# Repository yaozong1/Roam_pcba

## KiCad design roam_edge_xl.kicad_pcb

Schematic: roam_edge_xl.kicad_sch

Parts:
C1, C5, C48: 100nF; C_0402_1005Metric; MPN CL05B104KO5NNNC; LCSC Part C1525; not fitted
C2, C116: 100pf; C_0402_1005Metric; MPN 0402CG101J500NT; LCSC Part C1546
C3: 4.7uF; C_0603_1608Metric; MPN CL10A475MA8NQNC; Digi-key PN 445-6853-1-ND
C4, C8, C14, C15, C44, C56, C60, C72, C73, C100, C101, C110, C111, C112, C113, C115: 100nF; C_0402_1005Metric; MPN CL05B104KO5NNNC; LCSC Part C1525
C6: 47uF; L_1206_3216Metric; MPN CL31A476MPHNNNE; LCSC Part C96123
C7, C33, C34, C37: 100nF; C_0402_1005Metric; MPN CL05B104KP5NNNC; LCSC Part C133086
C9: DNP; C_0402_1005Metric; MPN #N/A; LCSC Part #N/A; not fitted
C10, C12, C18, C19, C35, C38, C62, C63: 33pF; L_0402_1005Metric; MPN GRM1555C1E330JA01D; LCSC Part C441758
C13, C24: 100nF; C_0603_1608Metric; Rating 100V, X7R; MPN GRM188R71H104KA93D; LCSC Part C77055
C17, C79: 1nF; C_0603_1608Metric; MPN CC0603KRX7R0BB102; LCSC Part C106247
C20, C25, C26, C27, C103, C104: 22uF; C_0805_2012Metric; MPN CL21A226MOQNNNE; LCSC Part C98190
C21, C81: 10nF; C_0603_1608Metric; MPN CC0603KRX7R0BB103; LCSC Part C107059
C23, C28, C83: 100nF; C_0603_1608Metric; Rating 100V, X7R; MPN CC0603KRX7R0BB104; LCSC Part C113803
C30: 470uF; C_Elec_6.3x7.7; MPN JVJ16V470M6x8; LCSC Part C46550400
C31, C32: 22uF; C_Elec_6.3x7.7; MPN JVJ100V22M6x8; LCSC Part C46550391
C36, C39: 10pF; C_0402_1005Metric; Rating C0G, NP0; MPN GJM1555C1H100FB01D; LCSC Part C782046
C40, C41: 10nF; C_0402_1005Metric; MPN CL05B103KB5NNNC; LCSC Part C15195
C42, C64, C65, C95, C96, C119, C120: 1uF; C_0402_1005Metric; MPN CL05A105KA5NQNC; LCSC Part C52923
C43, C82: 100nF; C_0402_1005Metric; MPN CL05B104KP5NNNC
C45: 10uF; C_0603_1608Metric; Rating X5R; MPN CL10A106MA8NRNC; Digi-key PN 445-6853-1-ND
C49, C67: 1uF; C_0402_1005Metric; MPN CL05A105KA5NQNC; LCSC Part C52923; not fitted
C55: 2.2uF; C_0402_1005Metric; MPN CL05A225MQ5NSNC; LCSC Part C12530
C59, C117: 10uF; C_0603_1608Metric; MPN CL10A106MA8NRNC; Digi-key PN 445-6853-1-ND
C66: 100nF; C_0402_1005Metric; MPN CL05B104KP5NNNC; not fitted
C77, C78: 100pF; C_0603_1608Metric; MPN CC0603JRNPO0BN101; LCSC Part C107033
C102, C108, C109: 10uF; C_0603_1608Metric; MPN CL10A106MO8NQNC; LCSC Part C92487
CP1, CP3: 100u; CP_EIA-6032-28_Kemet-C; MPN 593D107X9010C2TE3; LCSC Part C167094
CR1: SMCJ100A; SMCJSeries_LTF; MPN SMCJ100A
CR2: PLZ15C-G3/H; ZDO_15C-G3&slash_H_VIS; MPN PLZ15C-G3/H
D1: AXGD10402; D_0402_1005Metric; MPN AXGD10402KR; LCSC Part C434715; not fitted
D3, D4: LED; LED_0603_1608Metric; mpn QBLP601D-IB; LCSC Part C2286
D6, D8, D20: D4V5H1BS2LP-7B; D_0402_1005Metric; MPN D4V5H1BS2LP-7B; LCSC Part C5244624
D9: B230; D_SMB; MPN B230
D10: D_Schottky; D_SMA; MPN RB058L150TE25; LCSC Part C3020232
D11: SS10100; D_SMC; MPN SS10100-SMC; LCSC Part C908692
D12: SM712_SOT23; SOT-323_SC-70; MPN ESDCAN03-2BWY; LCSC Part C1973833
D13: AXGD10402; D_0402_1005Metric; MPN AXGD10402KR; LCSC Part C434715
D16: PESD8V0L2BT-N; SOT-23; MPN PESD8V0L2BT-N; LCSC Part C316022; not fitted
D17: BAT54AW; SOT-323_SC-70; MPN BAT54AW; LCSC Part C5186015
D21, D22: ESD56151W04; D_SOD-323; MPN TPESD56151W04; LCSC Part C2841421
D24: PESD3V3L1BA-N; D_SOD-323; MPN PESD3V3L1BA-N; LCSC Part C41409249
F1: Polyfuse; Fuse_1206_3216Metric; MPN SMD1206-300-6; LCSC part number C46641035
FID1, FID2: Fiducial; Fiducial_1mm_Mask2mm; MPN #N/A; LCSC Part #N/A; not fitted
IC4: MAX13487EESA+T; SOIC127P600X175-8N; MPN MAX13487EESA+T; Mouser Part Number 700-MAX13487EESAT; not fitted
J1: Battery; Molex_PicoBlade_53048-0310_1x03_P1.25mm_Horizontal; MPN 1.25T-3P-WP; LCSC Part C2689907
J2, J4: USB_B_Micro; USB_Micro-B_Molex_47346-0001; MPN 47346-0001; LCSC Part C132560; not fitted
J3: IPEX; IPEX-SMD_HC-RF-IPEX0303-01; MPN HC-RF-IPEX0303-01; LCSC Part C2894919
J5: DNP; Solder_conn_10p; not fitted
J6: CA-L01; MPN CA-L01; LCSC Part C2838841
J7: SIM8060-6-0-14-00-A; GCT_SIM8060-6-0-14-00-A; MPN SIM8060-6-0-14-00-A; Mouser Part Number 640-SIM8060601400A
J8: MX23A18NF1; CONN-TH_18P-P2.50_MX23A18NF1; MPN MX23A18NF1
J9: Conn_01x11_Pin; JST_XH_B11B-XH-A_1x11_P2.50mm_Vertical; MPN 2.54mm-11P ZZ; LCSC Part C18185680; not fitted
J11: Conn_01x06_Pin; PinHeader_1x06_P2.54mm_Vertical
JP2: 0; R_0805_2012Metric; MPN RC0805JR-070RL; LCSC Part C96345; not fitted
JP4: SolderJumper_2_Open; SolderJumper-2_P1.3mm_Open_RoundedPad1.0x1.5mm; LCSC Part #N/A; not fitted
JP5: SolderJumper_2_Open; SolderJumper-2_P1.3mm_Open_RoundedPad1.0x1.5mm; not fitted
L1: 2.2uH; L_Bourns-SRN4018; MPN WPN4020H2R2MT; LCSC Part C98361
L2: 18nH; L_0402_1005Metric; MPN LQW15AN18NG80D; LCSC Part C908004
L3: 2.2nH; L_0402_1005Metric; MPN LQW15AN2N2B80D; LCSC Part C2041833
L4: 4.3nH; L_0402_1005Metric; MPN LQG15HS4N3S02D; LCSC Part C97999
L5: 22nH; L_0402_1005Metric; MPN LQW15AN22NG00D; LCSC Part C86129
L6: 68nH; L_0402_1005Metric; MPN SDCL1005C68NJTDF; LCSC Part C32836
L8: 33UH; L_Changjiang_FNR5040S; MPN FNR5040S330MT; LCSC Part C167973
L10, L13: DNP; L_0402_1005Metric; MPN #N/A; LCSC Part #N/A; not fitted
L11: 1uH; IND-SMD_L5.0-W5.0_SPM5030T; MPN SPM5030T-1R0M; LCSC Part C138582
L12: 56UH; L_Changjiang_FXL1040; MPN FXL1040-330-M; LCSC Part C475918
L15: 2.2uH; L_0603_1608Metric; MPN CMH160808B2R2MT; LCSC Part C394950
Q1: SQS201CENW-T1_GE3; PDFN3333-8_L3.1-W3.2-P0.65-LS3.4-BL; MPN SQS201CENW-T1_GE3
Q4, Q5, Q6: Q_NPN_BEC_BRT; SOT-23; MPN KRC106S; LCSC Part C5439972
Q7: 2N7002E; SOT-23; MPN 2N7002E
Q9: AO4407A; AO4407A_SOIC-8_150MIL; Manufacturer_Part_Number AO4407A
R1: 15k; R_0402_1005Metric; MPN 0402WGF1502TCE; LCSC Part C25756
R2, R6, R30, R60: 1K; R_0402_1005Metric; MPN 0402WGF1001TCE; LCSC Part C11702
R3: 1K; R_0402_1005Metric; MPN 0402WGF1001TCE; LCSC Part C11702; not fitted
R4: 0; R_0402_1005Metric; MPN 0402WGF0000TCE; LCSC Part C17168
R5: 100k; R_0402_1005Metric
R7: 200K; R_0402_1005Metric; MPN HPCR0402F200KK9; LCSC Part C364966
R8: 24k; R_0402_1005Metric
R9, R10: 750; R_0603_1608Metric; MPN 0603WAF7500T5E; LCSC Part C23241
R11, R55, R56: 10K; R_0402_1005Metric; MPN 0402WGF1002TCE; LCSC Part C25744
R12, R34, R36, R100: 0; R_0402_1005Metric; MPN RC0402FR-070RL; LCSC Part C106231
R13, R80, R93: 100K; R_0402_1005Metric; MPN 0402WGF1003TCE; LCSC Part C25741
R14: 0.05; R_0805_2012Metric; MPN ERJL06KF50MV; LCSC Part C713441
R15: 12k; R_0402_1005Metric
R17: 169k; R_0402_1005Metric; MPN FRC0402F1693TS; LCSC Part C2974012
R18: 30K; R_0402_1005Metric; MPN RC0402FR-0730KL; LCSC Part C138008
R19, R29, R37, R38: 4K7; R_0402_1005Metric; MPN 0402WGF4701TCE; LCSC Part C25900
R20: 3.6K; R_0402_1005Metric; MPN ERJ2RKF3601X; LCSC Part C413090
R24: 1K; R_0603_1608Metric
R26: 1.2K; R_0402_1005Metric; MPN FRC0402F1201TS; LCSC Part C2909307
R27, R41: 10K; R_0603_1608Metric
R33, R35: 10K; R_0402_1005Metric; MPN 0402WGF1002TCE; LCSC Part C25744; not fitted
R39, R40: 20; R_0402_1005Metric; Tolerance 1%; MPN 0402WGF200JTCE; LCSC Part C25089; not fitted
R43, R45: 4K7; R_0402_1005Metric; MPN 0402WGF4701TCE; LCSC Part C25900; not fitted
R44: DNP; R_0402_1005Metric; MPN #N/A; LCSC Part #N/A; not fitted
R47, R48: 10; R_0402_1005Metric; MPN CRCW040210R0FKED; LCSC Part C481926; not fitted
R57: 680; R_0805_2012Metric; MPN ERJP06J681V; LCSC Part C441734
R58: 100k; R_0402_1005Metric; MPN 667-ERJ-2RKF1003X
R59: 1k; R_0402_1005Metric; MPN PFR05S-102-FNH
R61: 130; R_0603_1608Metric; MPN 0603WAF1300T5E; LCSC Part C22796
R62: 4K7; R_0402_1005Metric; LCSC Part C25900
R79: 649K; R_0402_1005Metric; MPN 0402WGF6493TCE; LCSC Part C423143
R84: 3.9K; R_0402_1005Metric; MPN 0402WGF3901TCE; LCSC Part C51721
R85: 51K; R_0402_1005Metric; MPN 0402WGF5102TCE; LCSC Part C25794
R86: 1.6K; R_0402_1005Metric; MPN 0402WGF1601TCE; LCSC Part C4908
R87: 0.2; R_0805_2012Metric; MPN 0805W8F200LT5E; LCSC Part C44051
R94: 330k; R_0402_1005Metric; MPN RC0402FR-07330KL; LCSC Part C138006
S1: ESE-11MV9; ESE11MV9; MPN ESE-11MV9; Mouser Part Number 667-ESE-11MV9
SW1: SW_Push; SW_Push_SPST_NO_Alps_SKRK; MPN TS-1088-AR02016; LCSC Part C720477
SW2: SW_Push; SW_Push_SPST_NO_Alps_SKRK; MPN TS-1088-AR02016; LCSC Part C720477; not fitted
TP1: TXD; TestPoint_Pad_D1.0mm; MPN #N/A; LCSC Part #N/A; not fitted
TP2, TP4, TP5, TP8, TP16, TP17, TP18, TP23, TP27, TP28: TestPoint; TestPoint_Pad_D1.0mm; MPN #N/A; LCSC Part #N/A; not fitted
TP3: T_BAT; TestPoint_Pad_D1.0mm; MPN #N/A; LCSC Part #N/A
TP6: TestPoint; TestPoint_Pad_D1.0mm; MPN #N/A; LCSC Part #N/A
TP9, TP12: TestPoint; TestPoint_Pad_D1.0mm; not fitted
TP10: RXD; TestPoint_Pad_D1.0mm; MPN #N/A; LCSC Part #N/A; not fitted
TP25, TP26: rs485_tx; TestPoint_Pad_D1.0mm; MPN #N/A; LCSC Part #N/A; not fitted
U1: NUP4202; SOT-363_SC-70-6; MPN NUP4202W1T2G; LCSC Part C22390024
U2: TXB0102DCU; VSSOP-8_2.3x2mm_P0.5mm; MPN TXB0102DCUR; LCSC Part C60709; not fitted
U3: TPS566242DRLR; MPN TPS566242DRLR; LCSC Part C5219277
U4: EG1192L; HTSOP-8-1EP_3.9x4.9mm_P1.27mm_EP2.4x3.2mm; MPN EG1192L; LCSC Part C2987436
U5, U19: LTV-217; SOIC-4_4.55x2.6mm_P1.27mm; MPN LTV-217-TP1-B-G; LCSC Part C481866
U6: W25Q128JVP; WSON-8-1EP_6x5mm_P1.27mm_EP3.4x4.3mm
U7: EG915UEUAC-N05-SNNSA; XCVR_EG915UEUAC-N05-SNNSA; MPN EG915UEUAC-N05-SNNSA; LCSC Part C7471302
U8: USBLC6-2SC6; SOT-23-6; MPN USBLC6-2SC6; LCSC Part C2827654
U10, U21, U27: LP5907MFX-3.3; SOT-23-5; MPN LP5907MFX-3.3/NOPB; LCSC Part C80670
U11: TXB0108RGY; Texas_RGY_R-PVQFN-N20_EP2.05x3.05mm; MPN TXB0108RGYR; LCSC Part C194701
U13: LIS2DH12TR; LIS12DH; MPN LIS2DH12TR; Digi-key PN DNP
U14: CN809L; SOT-23-3; MPN CN809L; LCSC Part C840517
U15, U16: LM66100DCKR; SOT-363_SC-70-6; MPN LM66100DCKR; LCSC Part C2869734
U18: TPS61022; Texas_RWU0007A_VQFN-7_2x2mm_P0.5mm; MPN TPS61022RWUR; LCSC Part C915088
U20: LC760Z; XCVR_LC79H; MPN #N/A; LCSC Part C9900159239
U22: TP4056; TP4056_SOP-8-PP; MPN TP4056; LCSC Part C382139
U25: ESP32-S3-MINI-1; ESP32-S2-MINI-1; MPN ESP32-S3-MINI-1-N8; LCSC Part C2913206
U26: TJA1051T/3; SOIC-8_3.9x4.9mm_P1.27mm; MPN TJA1051T/3; LCSC Part C38695
U28: USBLC6-2SC6; SOT-23-6; MPN USBLC6-2SC6; LCSC Part C2827654; not fitted

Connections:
3V3_ALWAYS_ON: C1.1, C14.1, C24.1, C44.1, C45.1, C96.1, C112.2, C117.1, R11.1, R37.1, R38.1, R55.2, R58.2, TP5.1 (1_1), U2.3 (VCCA), U2.6 (OE), U6.8 (VCC), U10.5 (OUT), U11.19 (V_{CCB}), U13.2 (CS), U13.9 (VDD), U13.10 (VDD_IO), U25.3 (3V3), U26.5 (VIO)
3V3_ANT: R4.2, TP23.1 (1_1), U20.14 (ANT_BIAS)
3V3_LDO: C72.1, C73.1, C120.1, R60.1, TP18.1 (1_1), U19.1, U27.5 (OUT)
4V0: C19.1, C20.1, C25.1, C26.1, C27.1, C33.1, C34.1, C35.1, C36.2, C37.1, C38.1, C39.2, CP1.1, CP3.1, D6.1 (K), L1.2, R17.1, TP8.1 (1_1), U7.32 (VBAT_BB), U7.33 (VBAT_BB), U7.52 (VBAT_RF), U7.53 (VBAT_RF)
4V7_BOOST: C100.1, C103.1, C104.1, R79.1, TP16.1 (1_1), U15.3 (~CE), U16.1 (VIN), U18.3 (VOUT)
5V0: C6.1, C7.1, C64.1, C95.1, C113.2, C119.1, J11.4, JP2.2, R8.1, TP2.1 (1_1), U3.1 (VIN), U10.1 (IN), U14.3 (VCC), U15.6 (VOUT), U16.6 (VOUT), U21.1 (IN), U26.3 (VCC), U27.1 (IN)
5V0_BUCK: C5.1, C30.1, C42.1, C48.1, C49.1, IC4.8 (VCC), JP2.1, L12.2, R3.1, R20.1, R30.2, R33.2, R35.2, R43.2, R87.1, TP27.1 (1_1), U2.7 (VCCB), U15.1 (VIN), U16.3 (~CE)
12V_MCU_OUT: J8.12, J11.5
/3V3_LDO_EN: U25.14 (IO10), U27.3 (EN)
/ACC_INT: U13.12 (INT_1), U25.34 (IO38)
/CAN_500_H: D12.1 (A1), J5.6, J8.2, J9.6, U26.7 (CANH)
/CAN_500_L: D12.2 (A2), J5.5, J8.3, J9.5, U26.6 (CANL)
/CAN_RXD: U25.35 (IO39), U26.4 (RXD)
/CAN_SHDN: R6.1, U25.37 (IO41)
/CAN_TXD: U25.36 (IO40), U26.1 (TXD)
/CHG_EN: R2.1, U25.8 (IO4)
/CONN_LED: D4.2 (A), U25.29 (IO34)
/CTS_1V8: U7.36 (MAIN_CTS), U11.5 (A4)
/CTS_3V3: U11.16 (B4), U25.10 (IO6)
/D+/A: D16.1 (A1), J5.7, J9.7, R47.1
/D-/B: D16.2 (A2), J5.8, J9.8, R48.1
/DCD_1V8: U7.38 (MAIN_DCD), U11.6 (A5)
/DCD_3V3: U11.15 (B5), U25.9 (IO5)
/EN: R56.1, R62.2, SW1.2, TP4.1 (1_1), U25.45 (EN)
/FLASH_CLK: U6.6 (CLK), U25.16 (IO12)
/FLASH_CS: U6.1 (~CS), U25.5 (IO1)
/FLASH_MISO: U6.2 (DO/IO_{1}), U25.17 (IO13)
/FLASH_MOSI: U6.5 (DI/IO_{0}), U25.15 (IO11)
/Flasher_Out: J8.4, J11.3
/GNSS_ANT: L13.2, R100.2, U20.11 (RF_IN)
/GNSS_BOOT: JP4.2 (B), U20.18 (BOOT)
/GNSS_EN: U21.3 (EN), U25.44 (IO46)
/GNSS_RESET: Q6.1 (B), U25.27 (IO47)
/GNSS_RXD: R36.1, U25.38 (IO42)
/GNSS_TXD: R34.1, U25.41 (IO45)
/IBL: C115.1, R93.2, R94.1, TP3.1 (1_1), U25.6 (IO2)
/IGN: D17.1, J5.10, J8.7, J9.10, J11.6, R57.1
/IGN_IN: R60.2, U5.4, U25.31 (IO35)
/IM_OUT: D17.2, J8.6, U19.4
/IM_OUT_3V3: R61.1, SW2.2, TP6.1 (1_1), U25.4 (IO0)
/JTAG_D+: J8.10, U25.24 (IO20), U28.1 (I/O1)
/JTAG_D-: J8.11, U25.23 (IO19), U28.3 (I/O2)
/LID_OPEN_DET: C43.1, S1.1 (NO_1), S1.2 (NO_2), U25.7 (IO3)
/MCU_TAMPER_CONN: C82.1, R59.1, U25.12 (IO8)
/MODEM_DTR_1V8: U7.30 (MAIN_DTR), U11.8 (A7)
/MODEM_DTR_3V3: U11.13 (B7), U25.26 (IO26)
/MODEM_RI_1V8: U7.39 (MAIN_RI), U11.7 (A6)
/MODEM_RI_3V3: U11.14 (B6), U25.28 (IO33)
/MODEM_RX_1V8: U7.34 (MAIN_RXD), U11.3 (A2)
/MODEM_RX_3V3: U11.18 (B2), U25.21 (IO17)
/MODEM_TX_1V8: U7.35 (MAIN_TXD), U11.1 (A1)
/MODEM_TX_3V3: U11.20 (B1), U25.22 (IO18)
/Modem_EN: R11.2, U3.5 (EN), U25.13 (IO9)
/NET_LED: U7.21 (NET_STATUS)
/NRESET: Q4.1 (B), U25.25 (IO21)
/NRF_LED: D3.2 (A), U25.33 (IO37)
/NTC: J1.3, R84.2, R85.1, U22.1 (TEMP)
/PPS_GNSS: U7.51 (PPS_GNSS)
/PSM_IND: U7.1 (PSM_IND)
/PWRKEY: Q5.1 (B), U25.20 (IO16)
/RF_ANT: C9.1, R12.1, U7.60 (ANT_MAIN)
/RF_ANT_OUT: D1.2 (A2), L2.2, L3.1, L4.1, L5.1, R12.2
/RS485_RX: U2.4 (A2)
/RS485_RX_5V: IC4.1 (RO), R35.1, TP25.1 (1_1), U2.1 (B2)
/RS485_TX: U2.5 (A1)
/RS485_TX_5V: IC4.4 (DI), R33.1, TP26.1 (1_1), U2.8 (B1)
/RTS_1V8: U7.37 (MAIN_RTS), U11.4 (A3)
/RTS_3V3: U11.17 (B3), U25.11 (IO7)
/RXD0: TP10.1 (1_1), U25.40 (RXD0)
/SCL: R38.2, U13.1 (SCL/SPC), U25.19 (IO15)
/SDA: R37.2, U13.4 (SDA/SDI/SDO), U25.18 (IO14)
/SIM_CLK: C12.1, J7.C3 (CLK), U1.1, U7.46 (USIM1_CLK)
/SIM_DATA: C18.1, J7.C7 (I/O), R1.1, U1.3, U7.45 (USIM1_DATA)
/SIM_RST: C10.1, J7.C2 (RST), U1.4, U7.44 (USIM1_RST)
/SIM_VDD: C8.1, J7.C1 (VCC), R1.2, U1.5, U7.43 (USIM1_VDD)
/STATUS_LED: U7.20 (STATUS), U11.9 (A8)
/STATUS_LED_3V3: R13.2, U11.12 (B8), U25.30 (IO48)
/T6_OUT: D9.1 (K), J5.9, J8.5, J9.9, Q9.5 (D_1), Q9.6 (D_2), Q9.7 (D_3), Q9.8 (D_4)
/T6_SIG: R24.2, R27.2, U25.32 (IO36)
/TAMPER_CONN: J8.9, R58.1, R59.2
/TXD0: TP1.1 (1_1), U25.39 (TXD0)
/USB_BOOT: JP5.2 (B), U7.75 (USB_BOOT)
/USB_DM: R40.2, U8.1 (I/O1)
/USB_DP: R39.2, U8.3 (I/O2)
/USB_VBUS: C66.1, C67.1, J2.1 (VBUS), U7.8 (USB_VBUS), U8.5 (VBUS)
GND: C1.2, C2.2, C3.2, C4.1, C5.2, C6.2, C7.2, C8.2, C9.2, C10.2, C12.2, C14.2, C15.2, C17.2, C18.2, C20.2, C21.2, C23.2, C24.2, C25.2, C26.2, C27.2, C28.2, C30.2, C31.2, C32.2, C33.2, C34.2, C35.2, C36.1, C37.2, C38.2, C39.1, C40.1, C41.1, C42.2, C43.2, C44.2, C45.2, C48.2, C49.2, C55.1, C56.2, C59.2, C60.1, C62.2, C63.2, C64.2, C65.2, C67.2, C72.2, C73.2, C78.2, C82.2, C83.2, C95.2, C96.2, C100.2, C101.2, C102.2, C103.2, C104.2, C108.2, C109.2, C110.2, C111.2, C112.1, C113.1, C115.2, C117.2, C119.2, C120.2, CP1.2, CP3.2, CR1.2, D6.2 (A), D8.2 (A), D9.2 (A), D11.2 (A), D12.3 (common), D13.1 (A1), D16.3 (A3), D17.3, D20.2 (A), D21.1 (A1), D22.1 (A1), D24.1 (A1), IC4.5 (GND), J1.1, J2.5 (GND), J2.6 (Shield), J3.2, J3.3, J3.4, J4.5 (GND), J4.6 (Shield), J5.2, J7.C5 (GND_1), J7.G1 (GND_2), J7.G2 (GND_3), J7.G3 (GND_4), J7.G4 (GND_5), J8.18, J9.2, J11.1, L2.1, L10.1, L13.1, L15.2, Q4.2 (E), Q5.2 (E), Q6.2 (E), Q7.2 (S), R5.2, R9.1, R10.1, R13.1, R15.2, R18.2, R26.2, R27.1, R29.2, R30.1, R45.1, R56.2, R80.2, R85.2, R86.2, R94.2, S1.C1 (COM_1), S1.C2 (COM_2), SW1.1, SW2.1, TP17.1 (1_1), TP28.1 (1_1), U1.2, U2.2 (GND), U3.3 (AGND), U3.4 (GND), U4.2 (GND), U5.3, U6.4 (GND), U7.3 (GND), U7.31 (GND), U7.47 (GND), U7.48 (GND), U7.50 (GND), U7.54 (GND), U7.55 (GND), U7.58 (GND), U7.59 (GND), U7.61 (GND), U7.62 (GND), U7.67 (GND), U7.68 (GND), U7.69 (GND), U7.70 (GND), U7.71 (GND), U7.72 (GND), U7.73 (GND), U7.74 (GND), U7.79 (GND), U7.80 (GND), U7.81 (GND), U7.82 (GND), U7.89 (GND), U7.90 (GND), U7.91 (GND), U7.100 (GND), U7.101 (GND), U7.102 (GND), U8.2 (GND), U10.2 (GND), U11.11 (GND), U11.21 (GND), U13.5 (RES), U13.6 (GND), U13.7 (GND), U13.8 (GND), U14.1 (GND), U15.2 (GND), U16.2 (GND), U18.1 (GND), U18.6 (MODE), U19.3, U20.1 (GND), U20.10 (GND), U20.12 (GND), U20.28 (GND), U21.2 (GND), U22.3 (GND), U22.PAD (GND), U25.1 (GND), U25.2 (GND), U25.42 (GND), U25.43 (GND), U25.46 (GND), U25.47 (GND), U25.48 (GND), U25.49 (GND), U25.50 (GND), U25.51 (GND), U25.52 (GND), U25.53 (GND), U25.54 (GND), U25.55 (GND), U25.56 (GND), U25.57 (GND), U25.58 (GND), U25.59 (GND), U25.60 (GND), U25.61 (GND), U25.62 (GND), U25.63 (GND), U25.64 (GND), U25.65 (GND), U26.2 (GND), U27.2 (GND), U28.2 (GND)
unnamed: C17.1, C79.2
unnamed: C21.1, C81.2
unnamed: C77.2, C78.1
unnamed: C2.1, C101.1, L6.1, R4.1
unnamed: C116.1, L10.2, R100.1
unnamed: D3.1 (K), R9.2
unnamed: D4.1 (K), R10.2
unnamed: D8.1 (K), TP9.1 (1_1), U7.23 (DBG_TXD)
unnamed: D10.1 (K), L8.1
unnamed: C13.1, D11.1 (K), L12.1, R14.1, U4.7 (VS)
unnamed: C116.2, D13.2 (A2), J3.1, L6.2
unnamed: D20.1 (K), TP12.1 (1_1), U7.22 (DBG_RXD)
unnamed: F1.2, Q1.5 (D), Q1.6 (D), Q1.7 (D), Q1.8 (D), Q1.9 (D)
unnamed: IC4.6 (A), R43.1, R44.2, R47.2
unnamed: IC4.7 (B), R44.1, R45.2, R48.2
unnamed: IC4.2 (~RE), IC4.3 (~SHDN), R3.2
unnamed: J2.3 (D+), R39.1
unnamed: J2.2 (D-), R40.1
unnamed: J4.3 (D+), U28.6 (I/O1)
unnamed: J4.2 (D-), U28.4 (I/O2)
unnamed: J4.1 (VBUS), U28.5 (VBUS)
unnamed: J5.3, J9.3
unnamed: J5.4, J9.4
unnamed: J6.2, L5.2
unnamed: J6.3, L3.2
unnamed: J6.4, L4.2
unnamed: JP4.1 (A), R29.1
unnamed: JP5.1 (A), R19.1
unnamed: L15.1, U5.2
unnamed: CR2.2, Q1.4 (G), R5.1
unnamed: C40.2, Q4.3 (C), U7.17 (~RESET)
unnamed: C41.2, Q5.3 (C), U7.15 (PWRKEY)
unnamed: Q6.3 (C), U20.9 (~RESET)
unnamed: Q7.3 (D), Q9.4 (G), R41.1
unnamed: Q7.1 (G), R24.1
unnamed: R57.2, U5.1
unnamed: R61.2, U19.2
unnamed: C19.2, R17.2, R18.1, U3.6 (FB)
unnamed: L1.1, U3.2 (SW)
unnamed: R7.2, U4.3 (EN)
unnamed: R20.2, R26.1, U4.5 (FB)
unnamed: R14.2, U4.8 (IS)
unnamed: C13.2, U4.6 (VB)
unnamed: R55.1, U6.3 (~WP/IO_{2}), U6.7 (~HOLD/~RESET/IO_{3})
unnamed: U7.10 (USB_DM), U8.6 (I/O1)
unnamed: U7.9 (USB_DP), U8.4 (I/O2)
unnamed: R8.2, R15.1, U10.3 (EN)
unnamed: R62.1, U14.2 (~RESET)
unnamed: R79.2, R80.1, U18.4 (FB)
unnamed: L11.2, U18.2 (SW)
unnamed: R36.2, U20.3 (RXD)
unnamed: R34.2, U20.2 (TXD)
unnamed: R2.2, U22.8 (CE)
unnamed: R86.1, U22.2 (PROG)
unnamed: C108.1, C110.1, R84.1, R87.2, U22.4 (VCC)
unnamed: R6.2, U26.8 (S)
VBAT: C102.1, C109.1, C111.1, J1.2, L11.1, R93.1, U18.5 (EN), U18.7 (VIN), U22.5 (BAT)
VCC_LC760Z: C3.1, C4.2, C56.1, C59.1, C60.2, C62.1, C63.1, C65.1, D21.2 (A2), D22.2 (A2), U20.6 (V_BCKP), U20.8 (VCC), U21.5 (OUT)
VDD_EXT: C15.1, C55.2, D24.2 (A2), R19.2, U7.29 (VDD_EXT), U11.2 (V_{CCA}), U11.10 (OE)
VIN: C23.1, C28.1, C31.1, C32.1, C83.1, L8.2, R7.1, U4.1 (VIN), U4.9 (VIN)
V_EXT: CR1.1, F1.1, J5.1, J8.1, J9.1
V_EXT_P: C77.1, C79.1, C81.1, CR2.1, D10.2 (A), J11.2, Q1.1 (S), Q1.2 (S), Q1.3 (S), Q9.1 (S_1), Q9.2 (S_2), Q9.3 (S_3), R41.2

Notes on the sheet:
I2C pull up
TODO Why so strong pullup?
Digital output motion sensor
3.3V OUTPUT
SIM_CLK is very important signal, the rise time and fall time of SIM_CLK should be less than 40ns. So the junction capacity of the TVS need to less 50pF.
600MA*600mA*0.2 = 72mW
Junction< 0.05pf TVS is needed Vrwm?
Rprog = 1100/Ibat 1.6k = 1100/690mA max charge current
Confirm this circuit works as designed, make sure the button above connects to GND when released. confirm height of the device vs button height
4V0 Buck GOOD TO KEEP CHEAP AND POWERFUL
Tamper connector. should be grounded to harness
Llv shift modem serial
ORing source selection circuit
90 Ohm differential pair
Battery interface
GSM / GNSS antenna an PI-network [ONLY PLACEHOLDER COMPONENTS]
RS485 input voltage is 4.75 which hits the edge of internal battery booster's output, so route it to 5v_buck to enhance the stability Then RS485 can only operate with external power
ACTIVE_LOW
0.3A
If = 15mA
F2 Keep cold res low High cold res will cause isses with the booster
If = 15mA STM32F105RB suck current limit = 25mA
VBAT_BB -> BaseBand 0.3A VBAT_RF -> RF POWER 1.3A Total 1.6A
VDD_EXT Vnom =1.8V Iout max 50mA
Flash memory
CAN
ESR < 0.7
Power dissipation R64 = 153mW
Connector
DURING DEVELOPENT ONLY
Unlcear if needed
For LM3671MF-3.3 Efficiency 85% when Vin=5v Vout=3.3 @10mA 80% when Vin=5v Vout=3.3 @1mA 60% when Vin=5v Vout=3.3 @0.1mA price =8RMB@JLC shall we remove it? LDO efficiency =~60%
1.2A
Vin -> buck Vbat -> boost
TVS is nice to have but a most if we add the choke to avoid high voltage spikes during a bus fault
MAX 50mA
Stand alone or all in one solution?
VEN = 1.2V
Vf = 1.4V GPIO_5 IGN_INPUT = 12 V (12V-1.4V)/0.015A =~ 680 Ohm
MODEM_UART

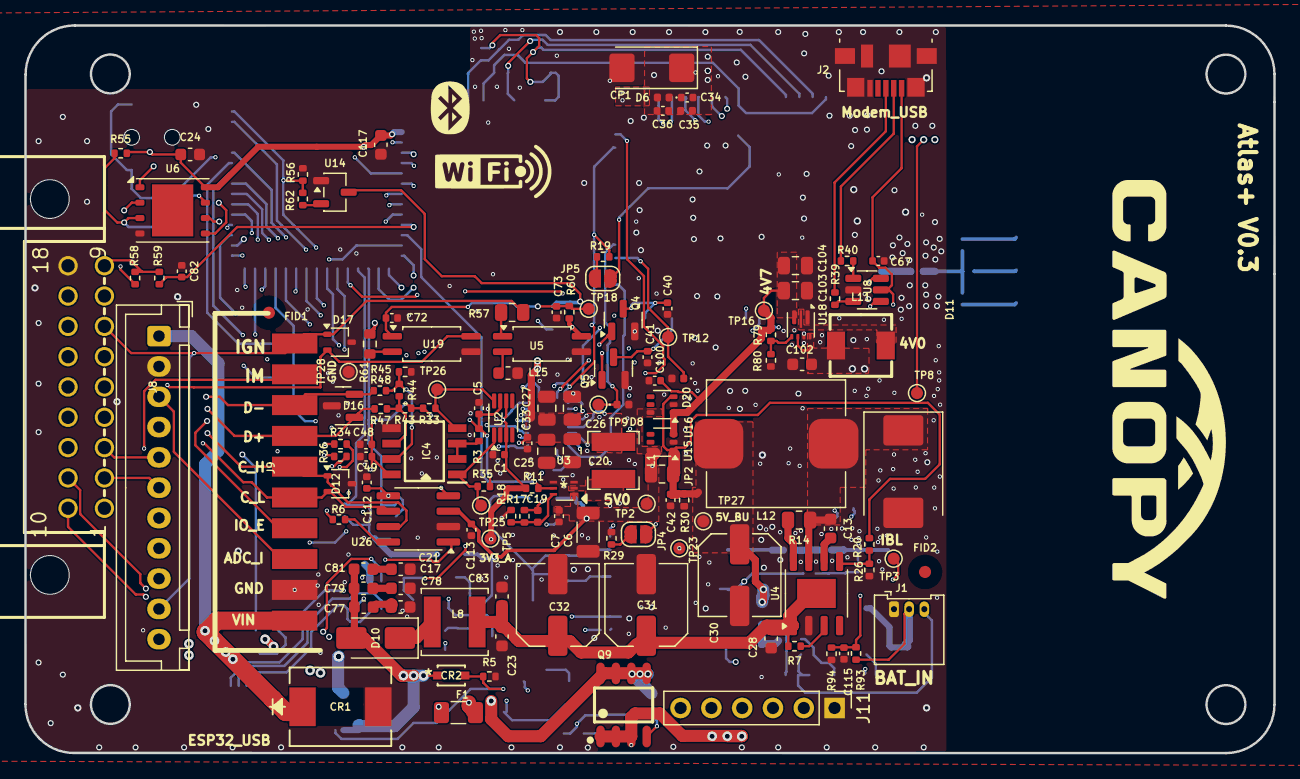
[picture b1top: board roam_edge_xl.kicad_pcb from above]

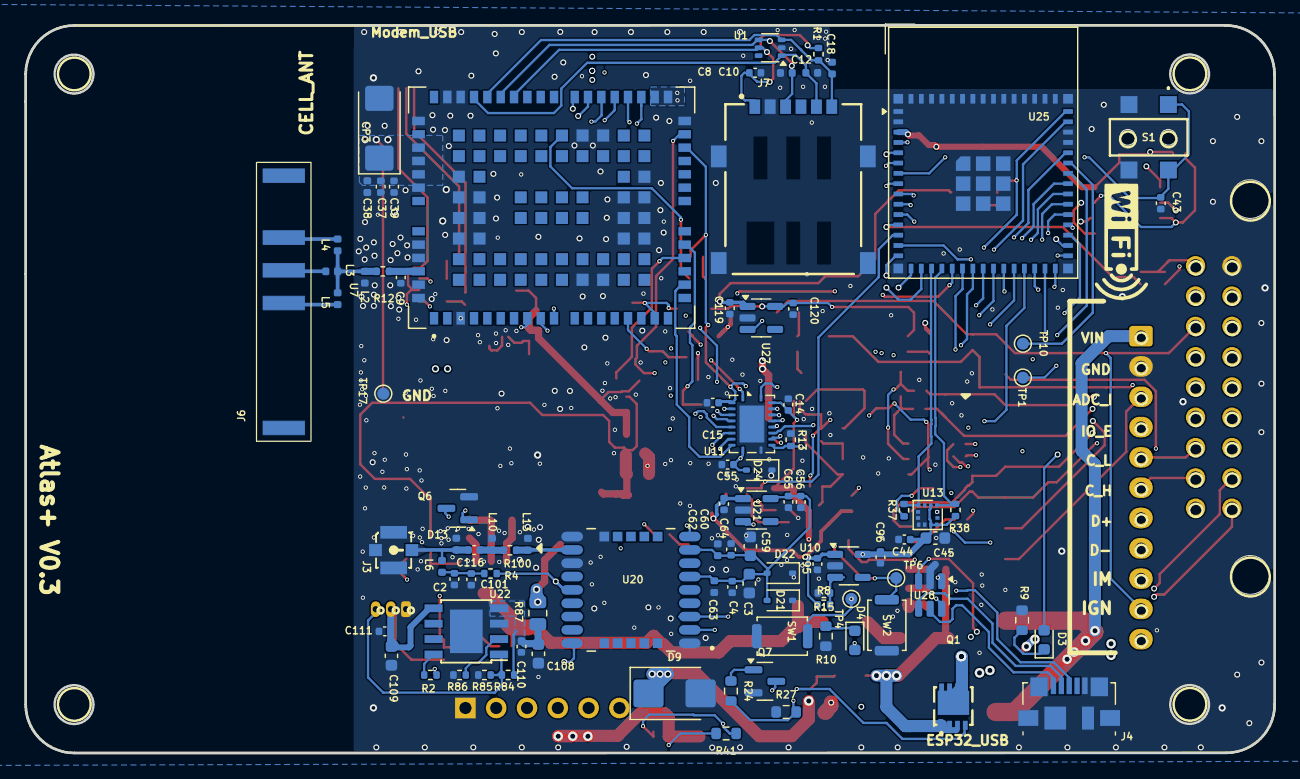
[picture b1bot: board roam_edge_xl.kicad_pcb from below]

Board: 6 copper layers, 103.0 x 60.0 mm, 231 parts (94 on the bottom side), 143 nets.

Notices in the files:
parts and their libraries:
Copyright 2021 Accelerated Designs. All rights reserved.
Copyright 2016 Accelerated Designs. All rights reserved.
